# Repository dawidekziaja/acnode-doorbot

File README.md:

# acnode-doorbot
A board designed to be used for ACNode and Doorbot at London Hackspace

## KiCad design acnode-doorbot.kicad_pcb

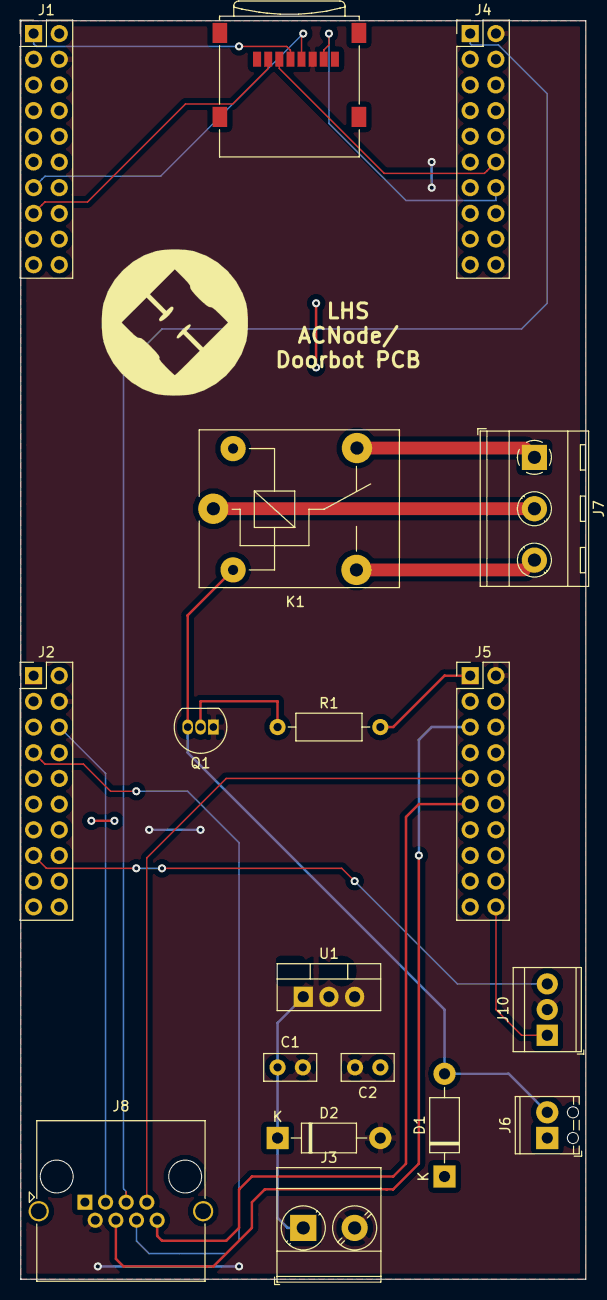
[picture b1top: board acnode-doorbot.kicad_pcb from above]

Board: 2 copper layers, 55.9 x 124.5 mm, 18 parts (0 on the bottom side), 23 nets.

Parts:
C1: 0.33uF; C_Disc_D5.0mm_W2.5mm_P2.50mm
C2: 0.1uF; C_Disc_D5.0mm_W2.5mm_P2.50mm
D1, D2: 1N4007; D_DO-41_SOD81_P10.16mm_Horizontal
J1, J2, J4, J5: Conn_02x10_Odd_Even; PinHeader_2x10_P2.54mm_Vertical
J3: Screw_Terminal_01x02; TerminalBlock_Phoenix_MKDS-3-2-5.08_1x02_P5.08mm_Horizontal
J6: Screw_Terminal_01x02; TerminalBlock_Phoenix_MPT-0,5-2-2.54_1x02_P2.54mm_Horizontal
J7: Screw_Terminal_01x03; TerminalBlock_RND_205-00288_1x03_P5.08mm_Horizontal
J8: RJ45; RJ45_Amphenol_RJHSE5380
J9: Micro_SD_Card; microSD_HC_Wuerth_693072010801
J10: Screw_Terminal_01x03; TerminalBlock_TE_282834-3_1x03_P2.54mm_Horizontal
K1: SANYOU_SRD_Form_C; Relay_SPDT_SANYOU_SRD_Series_Form_C
Q1: PN2222A; TO-92_Inline
R1: 1k; R_Axial_DIN0207_L6.3mm_D2.5mm_P10.16mm_Horizontal
U1: LM7805_TO220; TO-220-3_Vertical

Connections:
3.3V: J1.1, J2.1, J9.4
5V: C2.1, D1.1, J1.2, J2.2, J6.1, J8.1, K1.5, U1.3
12V: C1.1, D2.1, J3.1, U1.1
GND: C1.2, C2.2, D2.2, J1.4, J2.4, J3.2, J4.2, J5.2, J8.2, J9.6, J10.2, Q1.1, U1.2
unnamed: D1.2, J6.2, K1.2, Q1.3
unnamed: J7.1, K1.4
unnamed: J7.2, K1.1
unnamed: J7.3, K1.3
unnamed: Q1.2, R1.1
PB_4: J2.6, J8.3
PC_7: J1.15, J9.2
PD_0: J4.14, J9.7
PD_1: J4.12, J9.3
PD_3: J1.13, J9.5
PF_1: J4.1, J8.5
PG_1: J5.1, R1.2
PK_5: J5.5, J8.4
PM_1: J5.9, J8.7
PM_2: J5.11, J8.8
PM_6: J5.20, J10.1
PP_1: J2.7, J8.6
PP_4: J2.15, J10.3
RST: J4.10, J5.10

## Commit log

2018-10-11 Change of licence
2018-10-11 New licence
2018-12-02 Fixed multiple issues, bumped to rev 1.1
2018-12-04 Updated README.md with images
